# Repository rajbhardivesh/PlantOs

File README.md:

# 🌱 PlantOS – Smart IoT Plant Monitoring & Automation System

---

## 🚀 Overview

**PlantOS** is a complete **IoT-based plant monitoring and automation system** designed for real-world deployment.

It integrates:
- 📡 Embedded Firmware (ESP32)
- ⚡ Custom PCB Hardware
- 🌐 Web Dashboard
- ☁️ MQTT Cloud Communication

The system continuously monitors environmental conditions and automatically controls irrigation and lighting.

---

## 📸 Hardware Preview

Custom ESP32-based PCB for plant monitoring and automation.

---

## ✨ Key Features

### 🌡️ Multi-Sensor Monitoring
- DHT22 → Temperature & Humidity  
- DS18B20 → High-accuracy temperature  
- PT100 → Industrial temperature sensing  
- BH1750 → Light intensity (Lux)  
- MQ135 → Air quality monitoring  
- Soil Moisture Sensor  

---

### ⚡ Smart Automation
- 💧 Automatic irrigation based on soil moisture  
- 💡 Automatic lighting based on ambient lux  
- ⚙️ Relay-based control system  

---

### 🌐 IoT Connectivity
- WiFi provisioning via Serial interface  
- Secure MQTT communication (TLS supported)  
- Real-time JSON data streaming  

---

### 🧠 Intelligent Calibration System

Supports runtime calibration via commands:

```
cal dht_temp
cal soil
cal pt100
cal mq135
```

✔ Stored in non-volatile memory (NVS)  
✔ No need to reconfigure after reboot  

---

### 💡 LED Status Indicator

| State | Meaning |
|------|--------|
| 🔴 Solid | No WiFi |
| 🔴 Blinking | WiFi connected, MQTT disconnected |
| 🔵 Blinking | Fully connected |

---

## 🧱 Hardware Specifications

### 🔌 Microcontroller
- ESP32

### 🔁 Outputs
| Device | GPIO |
|------|------|
| Pump Relay | GPIO21 |
| Light Relay | GPIO19 |

### 📥 Inputs
| Sensor | GPIO |
|------|------|
| DHT22 | GPIO4 |
| BH1750 | GPIO25, GPIO26 |
| MQ135 | GPIO14 |
| DS18B20 | GPIO32 |
| Soil Sensor | GPIO33 |
| PT100 | GPIO36 |

---

## 📡 MQTT Configuration

### Default Settings

```json
{
  "server": "f388acb36bf542b69c0c3cb96cb2cb16.s1.eu.hivemq.cloud",
  "port": 8883,
  "user": "plantos",
  "topic": "device/RDH001/data"
}
```

---

## 📊 Data Format (Published JSON)

```json
{
  "ssid": "YourWiFi",
  "dht_temp": 28.5,
  "dht_hum": 60.2,
  "soil_pct": 45.0,
  "lux": 320.5,
  "mq135": 210,
  "ds18b20": 27.1,
  "pt100": 26.9,
  "relay1": true,
  "relay2": false
}
```

---

## 🧩 Repository Structure

```
root/
│
├── index.html          # 🌐 Web Dashboard
├── web/src             # Frontend (JS, CSS)
├── pcb/source          # PCB Design Files
├── firmware            # ESP32 Firmware
```

---

## ⚙️ Setup Guide

### 1. Flash Firmware
- Open in Arduino IDE / PlatformIO  
- Select ESP32 board  
- Upload firmware  

### 2. Configure WiFi

Open Serial Monitor (115200 baud):

```
connect
```

### 3. Configure MQTT (Optional)

```
connect mqtt
```

### 4. Launch Dashboard

Open:
```
index.html
```

---

## 📟 Serial Commands

| Command | Description |
|--------|------------|
| connect | Scan WiFi |
| connect mqtt | Configure MQTT |
| status | System status |
| help | Show commands |
| cal <sensor> | Calibrate |

---

## 🔄 Automation Logic

### Pump
- ON → Soil < 25%
- OFF → Soil > 80%

### Light
- ON → Lux < 200
- OFF → Lux > 10000

---

## 🧠 Firmware Highlights

- Non-blocking state machine
- Auto reconnect WiFi
- MQTT keep-alive
- Persistent storage (NVS)
- JSON telemetry system

---

## 🌍 Use Cases

- Smart Agriculture
- Greenhouses
- Indoor Plants
- Research Labs
- Industrial IoT

---

## 📈 Future Roadmap

- Mobile App
- OTA Updates
- Cloud Dashboard
- LoRa Mode
- AI Automation

---

## Speacial  Thanks To 
PCB Design :  Rajbhar Divesh
Firmware & Web Dashboard: Varikar Manan 
 : 
## Author
** Varikar Manan **
## back-end Author 
** himanshu dave **

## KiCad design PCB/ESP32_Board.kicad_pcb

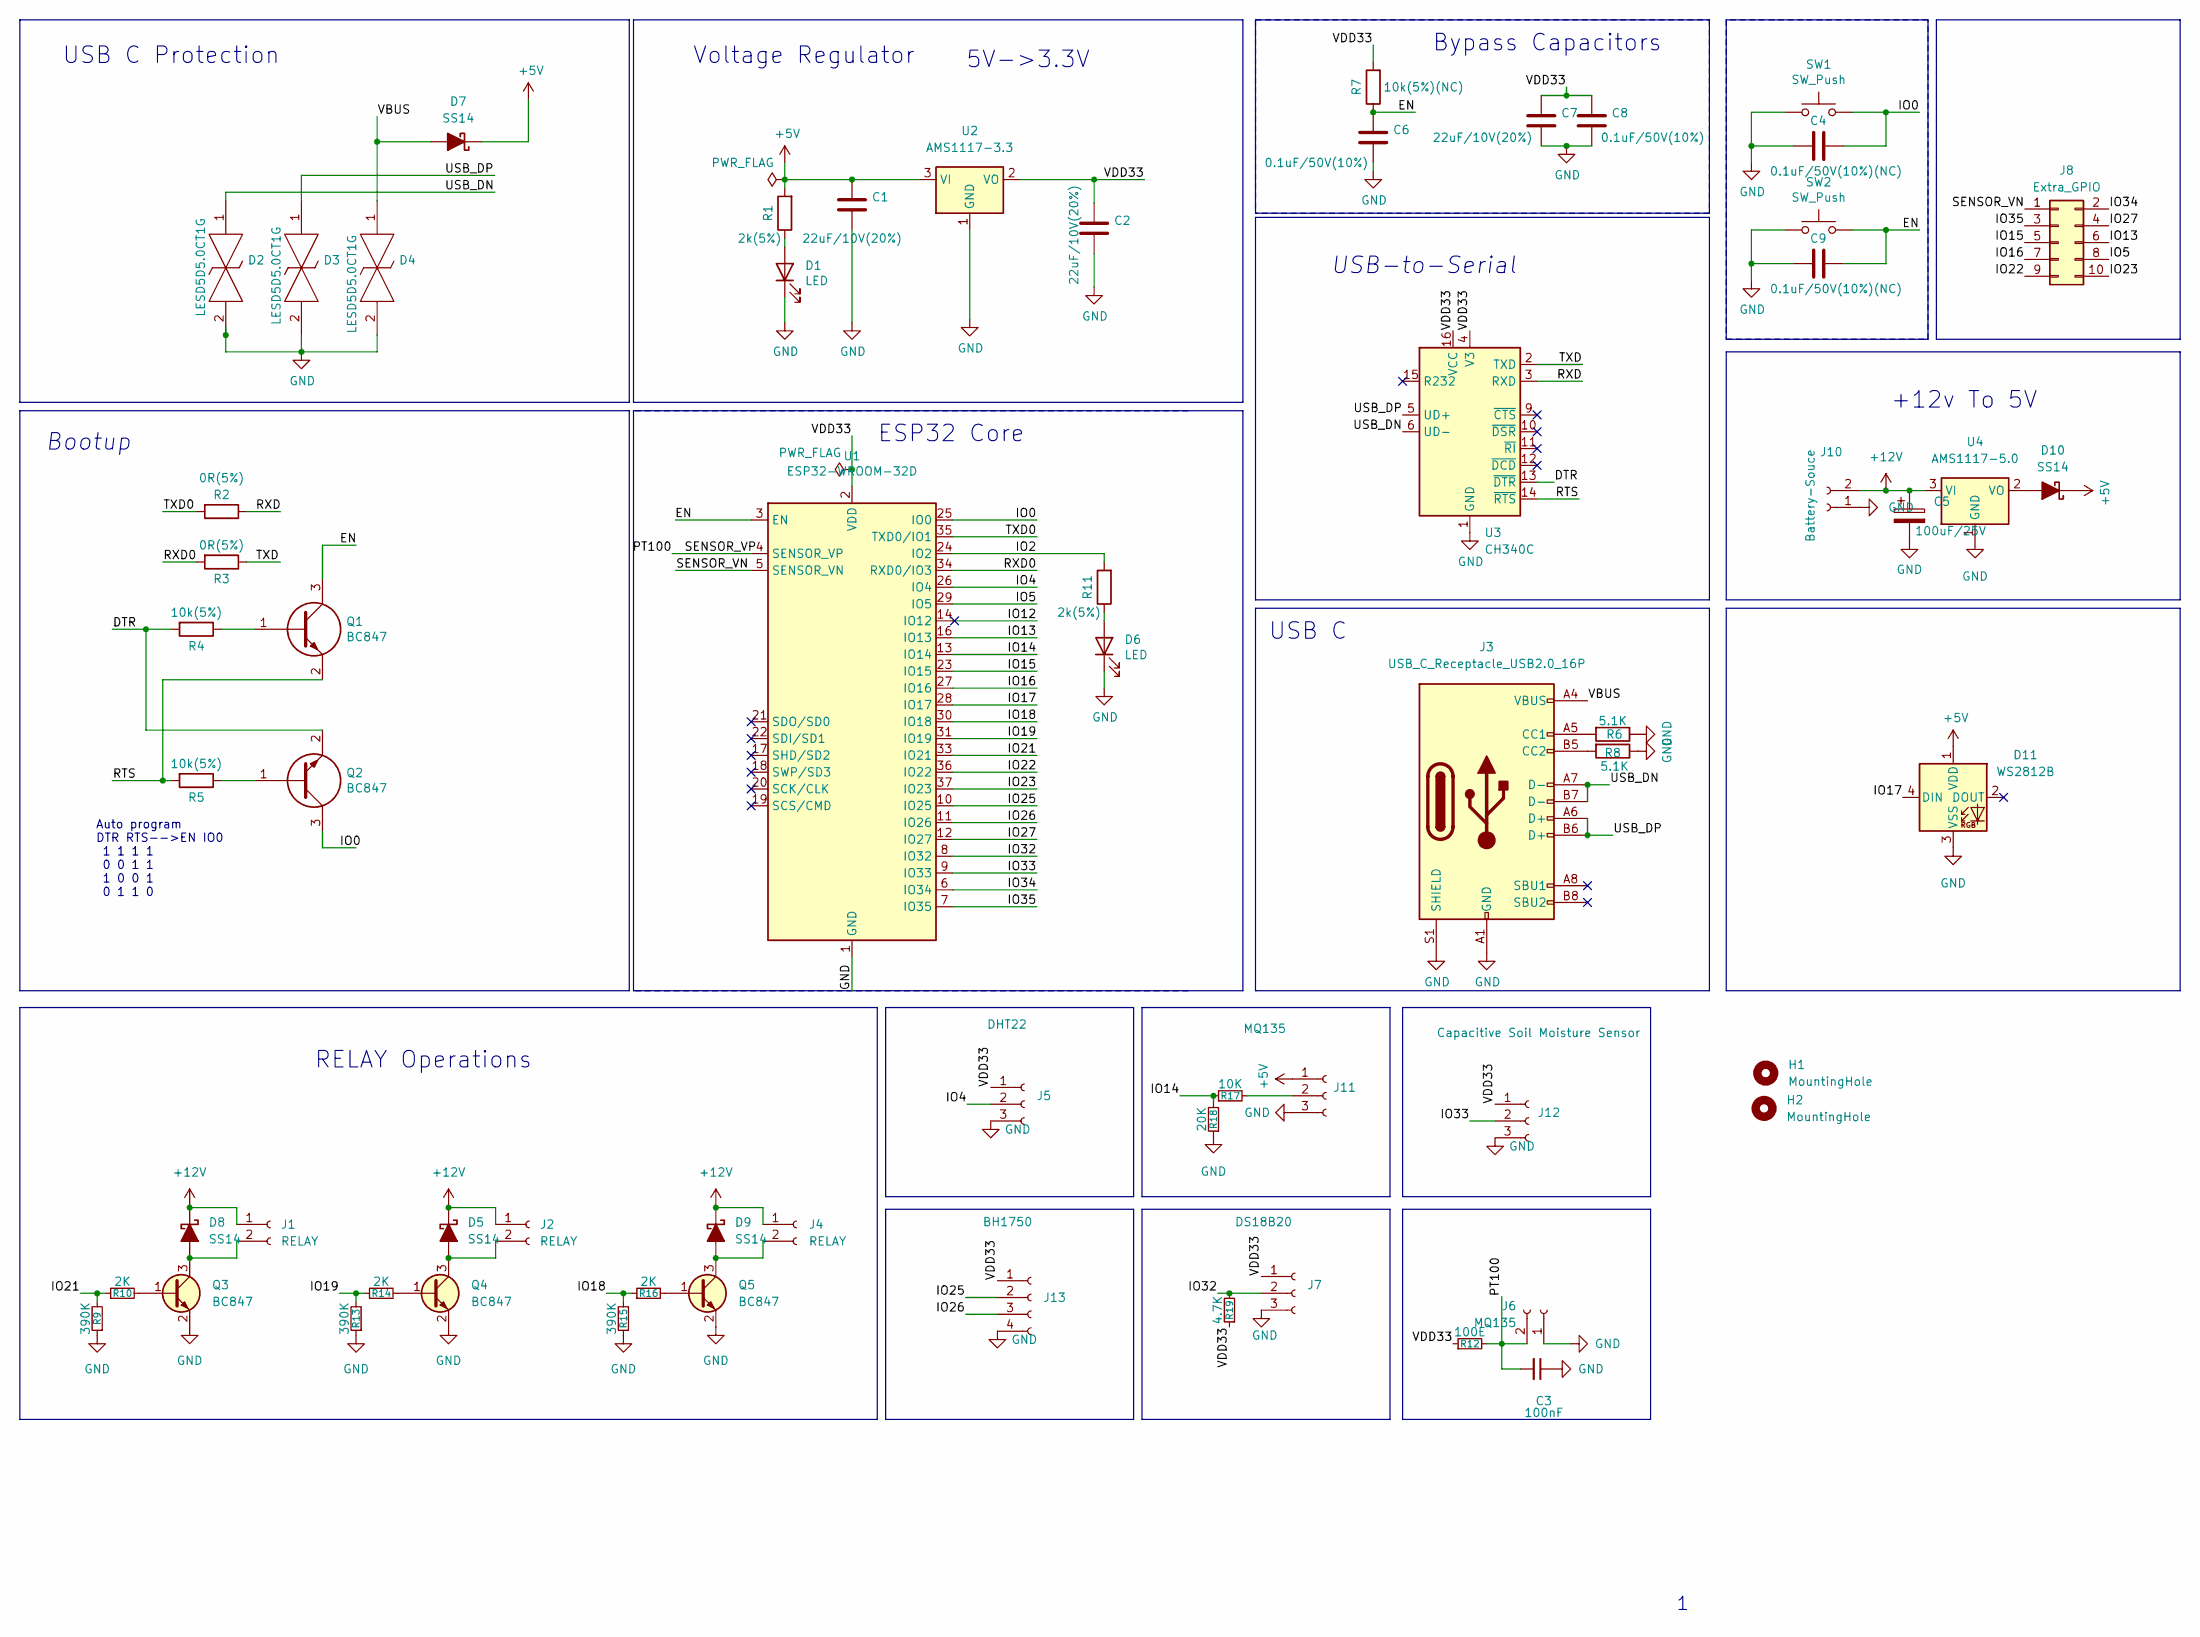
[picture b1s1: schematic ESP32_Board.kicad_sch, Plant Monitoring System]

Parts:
C1, C2, C7: 22uF/10V(20%); C_0805_2012Metric_Pad1.18x1.45mm_HandSolder
C3: 100nF; C_0805_2012Metric_Pad1.18x1.45mm_HandSolder
C4, C9: 0.1uF/50V(10%)(NC); C_0805_2012Metric_Pad1.18x1.45mm_HandSolder
C5: 100uF/25V; CP_Elec_6.3x7.7
C6, C8: 0.1uF/50V(10%); C_0805_2012Metric_Pad1.18x1.45mm_HandSolder
D1, D6: LED; LED_0805_2012Metric_Pad1.15x1.40mm_HandSolder
D2, D3, D4: LESD5D5.0CT1G; LESD5D50CT1G; Manufacturer_Part_Number LESD5D5.0CT1G
D5, D7, D8, D9, D10: SS14; D_SOD-123
D11: WS2812B; LED_WS2812B_PLCC4_5.0x5.0mm_P3.2mm
H1, H2: MountingHole; MountingHole_3.2mm_M3
J1, J2, J4: RELAY; JST_PH_B2B-PH-K_1x02_P2.00mm_Vertical
J3: USB_C_Receptacle_USB2.0_16P; USB_C_Receptacle_GCT_USB4105-xx-A_16P_TopMnt_Horizontal
J5: DHT22; JST_PH_B3B-PH-K_1x03_P2.00mm_Vertical
J6: MQ135; JST_PH_B2B-PH-K_1x02_P2.00mm_Vertical
J7: DS18B20; JST_PH_B3B-PH-K_1x03_P2.00mm_Vertical
J8: Extra_GPIO; PinHeader_2x05_P2.54mm_Vertical
J10: Battery-Souce; JST_PH_B2B-PH-K_1x02_P2.00mm_Vertical
J11: MQ135; JST_PH_B3B-PH-K_1x03_P2.00mm_Vertical
J12: Capacitive Soil Moisture Sensor; JST_PH_B3B-PH-K_1x03_P2.00mm_Vertical
J13: BH1750; JST_PH_B4B-PH-K_1x04_P2.00mm_Vertical
Q1, Q2: BC847; SOT-23; Manufacturer_Part_Number SS8050-G; Mouser Part Number 750-SS8050-G
Q3, Q4, Q5: BC847; SOT-23
R1, R11: 2k(5%); R_0805_2012Metric_Pad1.20x1.40mm_HandSolder
R2, R3: 0R(5%); R_0805_2012Metric_Pad1.20x1.40mm_HandSolder
R4, R5: 10k(5%); R_0805_2012Metric_Pad1.20x1.40mm_HandSolder
R6, R8: 5.1K; R_0805_2012Metric_Pad1.20x1.40mm_HandSolder
R7: 10k(5%)(NC); R_0805_2012Metric_Pad1.20x1.40mm_HandSolder
R9, R13, R15: 390K; R_0805_2012Metric_Pad1.20x1.40mm_HandSolder
R10, R14, R16: 2K; R_0805_2012Metric_Pad1.20x1.40mm_HandSolder
R12: 100E; R_0805_2012Metric_Pad1.20x1.40mm_HandSolder
R17: 10K; R_0805_2012Metric_Pad1.20x1.40mm_HandSolder
R18: 20K; R_0805_2012Metric_Pad1.20x1.40mm_HandSolder
R19: 4.7K; R_0805_2012Metric_Pad1.20x1.40mm_HandSolder
SW1, SW2: SW_Push; SW_SPST_TS-1088-xR020
U1: ESP32-WROOM-32D; ESP32-WROOM-32
U2: AMS1117-3.3; SOT-223-3_TabPin2
U3: CH340C; SOIC-16_3.9x9.9mm_P1.27mm
U4: AMS1117-5.0; SOT-223-3_TabPin2

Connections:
+5V: C1.1, D7.1 (K), D10.1 (K), D11.1 (VDD), J11.1, R1.2, U2.3 (VI)
+12V: C5.1, D5.1 (K), D8.1 (K), D9.1 (K), J1.1, J2.1, J4.1, J10.2, U4.3 (VI)
/DTR: Q2.2, R4.2, U3.13 (~DTR)
/EN: C6.1, C9.2, Q1.3, R7.1, SW2.2, U1.3 (EN)
/IO0: C4.2, Q2.3, SW1.2, U1.25 (IO0)
/IO2: R11.2, U1.24 (IO2)
/IO4: J5.2, U1.26 (IO4)
/IO5: J8.8, U1.29 (IO5)
/IO12: U1.14 (IO12)
/IO13: J8.6, U1.16 (IO13)
/IO14: R17.1, R18.2, U1.13 (IO14)
/IO15: J8.5, U1.23 (IO15)
/IO16: J8.7, U1.27 (IO16)
/IO17: D11.4 (DIN), U1.28 (IO17)
/IO18: R15.2, R16.1, U1.30 (IO18)
/IO19: R13.2, R14.1, U1.31 (IO19)
/IO21: R9.2, R10.1, U1.33 (IO21)
/IO22: J8.9, U1.36 (IO22)
/IO23: J8.10, U1.37 (IO23)
/IO25: J13.2, U1.10 (IO25)
/IO26: J13.3, U1.11 (IO26)
/IO27: J8.4, U1.12 (IO27)
/IO32: J7.2, R19.2, U1.8 (IO32)
/IO33: J12.2, U1.9 (IO33)
/IO34: J8.2, U1.6 (IO34)
/IO35: J8.3, U1.7 (IO35)
/PT100: C3.2, J6.2, R12.2, U1.4 (SENSOR_VP)
/RTS: Q1.2, R5.2, U3.14 (~RTS)
/RXD: R2.1, U3.3 (RXD)
/RXD0: R3.2, U1.34 (RXD0/IO3)
/SENSOR_VN: J8.1, U1.5 (SENSOR_VN)
/TXD: R3.1, U3.2 (TXD)
/TXD0: R2.2, U1.35 (TXD0/IO1)
/USB_DN: D2.1, J3.A7 (D-), J3.B7 (D-), U3.6 (UD-)
/USB_DP: D3.1, J3.A6 (D+), J3.B6 (D+), U3.5 (UD+)
/VBUS: D4.1, D7.2 (A), J3.A4 (VBUS), J3.A9 (VBUS), J3.B4 (VBUS), J3.B9 (VBUS)
/VDD33: C2.1, C7.1, C8.1, J5.1, J7.1, J12.1, J13.1, R7.2, R12.1, R19.1, U1.2 (VDD), U2.2 (VO), U3.4 (V3), U3.16 (VCC)
GND: C1.2, C2.2, C3.1, C4.1, C5.2, C6.2, C7.2, C8.2, C9.1, D1.1 (K), D2.2, D3.2, D4.2, D6.1 (K), D11.3 (VSS), J3.A1 (GND), J3.A12 (GND), J3.B1 (GND), J3.B12 (GND), J3.S1 (SHIELD), J5.3, J6.1, J7.3, J10.1, J11.3, J12.3, J13.4, Q3.2 (E), Q4.2 (E), Q5.2 (E), R6.1, R8.1, R9.1, R13.1, R15.1, R18.1, SW1.1, SW2.1, U1.1 (GND), U1.15 (GND), U1.38 (GND), U1.39 (GND), U2.1 (GND), U3.1 (GND), U4.1 (GND)
unnamed: D1.2 (A), R1.1
unnamed: D5.2 (A), J2.2, Q4.3 (C)
unnamed: D6.2 (A), R11.1
unnamed: D8.2 (A), J1.2, Q3.3 (C)
unnamed: D9.2 (A), J4.2, Q5.3 (C)
unnamed: D10.2 (A), U4.2 (VO)
unnamed: J3.A5 (CC1), R6.2
unnamed: J3.B5 (CC2), R8.2
unnamed: J11.2, R17.2
unnamed: Q1.1, R4.1
unnamed: Q2.1, R5.1
unnamed: Q3.1 (B), R10.2
unnamed: Q4.1 (B), R14.2
unnamed: Q5.1 (B), R16.2

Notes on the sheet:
Bypass Capacitors
+12v To 5V
USB C Protection
RELAY Operations
Auto program DTR RTS-->EN IO0 1 1 1 1 0 0 1 1 1 0 0 1 0 1 1 0
Bootup
USB-to-Serial
Voltage Regulator
ESP32 Core
5V->3.3V
USB C

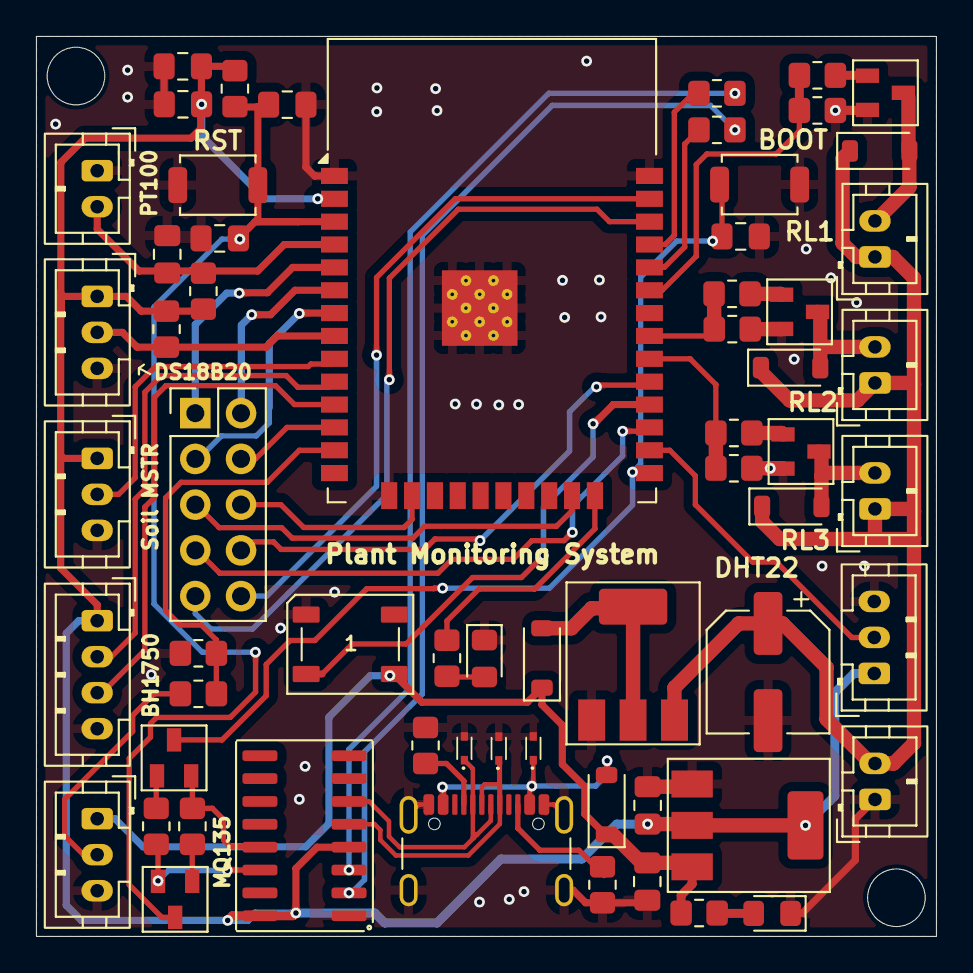
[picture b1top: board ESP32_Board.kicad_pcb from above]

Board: 2 copper layers, 50.0 x 50.0 mm, 64 parts (0 on the bottom side), 51 nets.

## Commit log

2026-05-05 initial Update
2026-05-05 Create CNAME
2026-05-05 Kicad PCB
2026-05-05 Schematic
2026-05-05 Source Code
2026-05-19 Add back-end author to README

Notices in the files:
README.md:
License: MIT
